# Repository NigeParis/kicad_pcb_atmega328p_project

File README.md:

# Schematic Bill of Materials

| Reference | Qty | Value | Footprint | Datasheet |
|-----------|-----|-------|-----------|-----------|
| C1, C2 | 2 | 12 pF | SMD_603 | [Yageo X7R](https://yageogroup.com/content/datasheet/asset/file/UPY-GPHC_X7R_6_3V-TO-250V) |
| C3 | 1 | 100 nF | SMD_603 | [Yageo X7R](https://yageogroup.com/content/datasheet/asset/file/UPY-GPHC_X7R_6_3V-TO-250V) |
| C4, C7 | 2 | 100 nF | SMD_603 | [Yageo X7R](https://yageogroup.com/content/datasheet/asset/file/UPY-GPHC_X7R_6_3V-TO-250V) |
| C6 | 1 | 1 µF | SMD_603 | [Yageo X7R](https://yageogroup.com/content/datasheet/asset/file/UPY-GPHC_X7R_6_3V-TO-250V) |
| D1 | 1 | LED Green | SMD_603 | [KP-1608ID](https://cdn-reichelt.de/documents/datenblatt/A500/KP-1608ID(VER.9A).pdf) |
| D2 | 1 | LED Red | SMD_603 | [KP-1608ID](https://cdn-reichelt.de/documents/datenblatt/A500/KP-1608ID(VER.9A).pdf) |
| J1 | 1 | Connector | J1_connector | [Samtec TSW](https://suddendocs.samtec.com/catalog_english/tsw_th.pdf) |
| J2 | 1 | Connector | J2_connector | [Samtec TSW](https://suddendocs.samtec.com/catalog_english/tsw_th.pdf) |
| J3 | 1 | FTDI | TSW-106-08-L-S-RA | [Samtec TSW](https://suddendocs.samtec.com/catalog_english/tsw_th.pdf) |
| R1 | 1 | 330 Ω | SMD_603 | [Yageo RC](https://yageogroup.com/content/datasheet/asset/file/PYU-RC_GROUP_51_ROHS_L) |
| R2, R3 | 2 | 10 kΩ | SMD_603 | [Yageo RC](https://yageogroup.com/content/datasheet/asset/file/PYU-RC_GROUP_51_ROHS_L) |
| SW1 | 1 | Push Switch | B3U-1000P(M) | [Omron B3U](https://omronfs.omron.com/en_US/ecb/products/pdf/en-b3u.pdf) |
| U1 | 1 | ATmega328P-A | TQFP-32 | [Microchip](https://ww1.microchip.com/downloads/aemDocuments/documents/corporate-responsibilty/environmental/material-compliance-documents/32L_TQFP_7x7x1_0mm_PT_C04-00074c.pdf) |
| Y1 | 1 | 16 MHz Crystal | SMD3225-4P | [X322516MLB4SI](https://www.lcsc.com/datasheet/C13738.pdf) |

## Summary

| Category | Count |
|----------|-------|
| Capacitors (C) | 6 |
| Diodes / LEDs (D) | 2 |
| Connectors (J) | 3 |
| Resistors (R) | 3 |
| Switch (SW) | 1 |
| Microcontroller (U) | 1 |
| Crystal (Y) | 1 |
| **Total components** | **17** |

# Pinout — Schematic (ATmega328P-A)

## J1 (12-pin, left connector)

| Pin | Signal |
|-----|--------|
| 12  | TXO    |
| 11  | RXI    |
| 10  | RST    |
| 9   | GND    |
| 8   | D2     |
| 7   | D3     |
| 6   | D4     |
| 5   | D5     |
| 4   | D6     |
| 3   | D7     |
| 2   | D8     |
| 1   | D9     |

---

## J2 (12-pin, right connector)

| Pin | Signal |
|-----|--------|
| 1   | RAW    |
| 2   | GND    |
| 3   | RST    |
| 4   | VCC    |
| 5   | A3     |
| 6   | A2     |
| 7   | A1     |
| 8   | A0     |
| 9   | SCK    |
| 10  | MISO   |
| 11  | MOSI   |
| 12  | D10    |

---

## J3 — FTDI (6-pin)

| Pin | Signal |
|-----|--------|
| 6   | GND    |
| 5   | GND    |
| 4   | VCC    |
| 3   | RXI    |
| 2   | TXO    |
| 1   | DTR    |

## 0603 SMD LED

**Imperial:** 0603 | **Metric equivalent:** 1608  
**Dimensions:** 1.6 × 0.8 × 0.8 mm (L × W × H)

### Top View

```
           1.6 mm
   ┌───────────────────┐
   │                   │  0.8 mm
   │   ╔═══════════╗   │
   │   ║    DIE    ║   │
   │   ╚═══════════╝   │
   │                   │
   └───────────────────┘
   [+]              [-]
  Anode           Cathode
```

### Dimensions Summary

| Parameter        | Value      |
|-----------------|------------|
| Length (L)       | 1.6 mm     |
| Width (W)        | 0.8 mm     |
| Height (H)       | 0.8 mm     |
| Pad size (each)  | ~0.8 × 0.9 mm |
| Pad pitch        | ~0.8 mm    |

### Notes
- Machine assembly strongly recommended; hand-soldering possible but challenging
- Typical forward current: 20 mA
- Typical forward voltage: 2.0–3.5 V (color-dependent)
- Cathode typically marked with a dot, triangle, or band on the package

## Soldered another PCB but even smaller </br>
The atmega328P-au was hard to do, had to resolder it 5 times until placed exactly on the pads.</br>
size of the MCU is 7mm x 7mm and 32 pads </br>
example size of a LED 

# SMD LED Package Dimensions: 0402 & 0603

> Imperial package codes — dimensions in **millimeters (mm)**

---

## 0402 SMD LED

**Imperial:** 0402 | **Metric equivalent:** 1005  
**Dimensions:** 1.0 × 0.5 × 0.5 mm (L × W × H)

### Top View

```
        1.0 mm
   ┌─────────────┐
   │             │  0.5 mm
   │  ╔═══════╗  │
   │  ║  DIE  ║  │
   │  ╚═══════╝  │
   │             │
   └─────────────┘
   [+]         [-]
  Anode      Cathode
```

### Dimensions Summary

| Parameter        | Value     |
|-----------------|-----------|
| Length (L)       | 1.0 mm    |
| Width (W)        | 0.5 mm    |
| Height (H)       | 0.5 mm    |
| Pad size (each)  | ~0.5 × 0.5 mm |
| Pad pitch        | ~0.6 mm   |

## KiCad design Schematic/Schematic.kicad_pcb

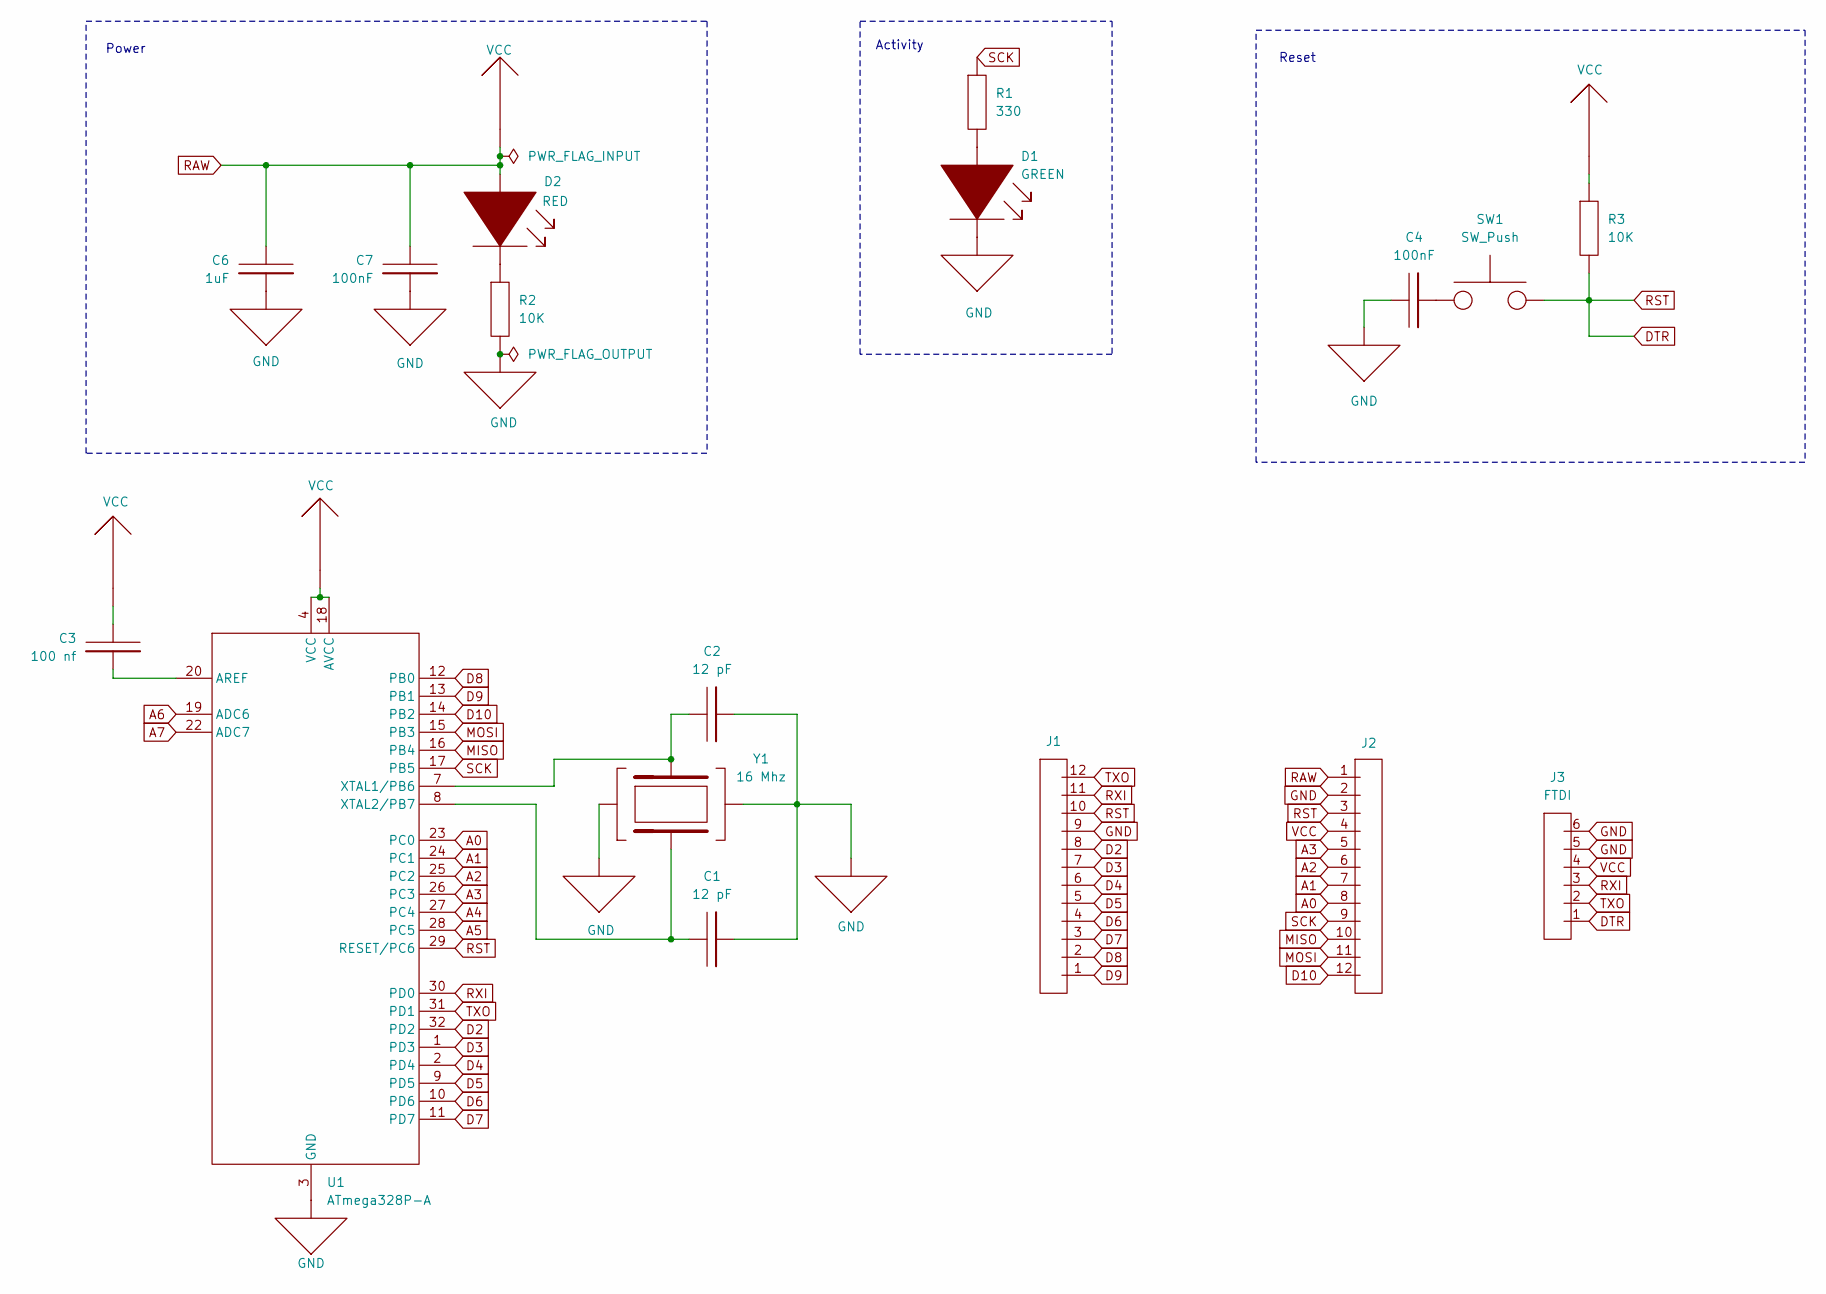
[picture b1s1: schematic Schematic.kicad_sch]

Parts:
C1, C2: 12 pF; SMD_603
C3: 100 nf; SMD_603
C4, C7: 100nF; SMD_603
C6: 1uF; SMD_603
D1: GREEN; SMD_603
D2: RED; SMD_603
J1: J1_connector
J2: J2_connector
J3: FTDI; FDTI_conector_TSW-106-08-L-S-RA
R1: 330; SMD_603
R2, R3: 10K; SMD_603
SW1: SW_Push; interupter_SMD_B3U-1000P(M)
U1: ATmega328P-A; atMega328P
Y1: 16 Mhz; Oscillator_SMD3225-4P_X322516MLB4SI

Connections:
A0: J2.8, U1.23 (PC0)
A1: J2.7, U1.24 (PC1)
A2: J2.6, U1.25 (PC2)
A3: J2.5, U1.26 (PC3)
A4: U1.27 (PC4)
A5: U1.28 (PC5)
A6: U1.19 (ADC6)
A7: U1.22 (ADC7)
D2: J1.8, U1.32 (PD2)
D3: J1.7, U1.1 (PD3)
D4: J1.6, U1.2 (PD4)
D5: J1.5, U1.9 (PD5)
D6: J1.4, U1.10 (PD6)
D7: J1.3, U1.11 (PD7)
D8: J1.2, U1.12 (PB0)
D9: J1.1, U1.13 (PB1)
D10: J2.12, U1.14 (PB2)
DTR: J1.10, J2.3, J3.1, R3.2, SW1.2, U1.29 (RESET/PC6)
GND: C1.2, C2.2, C4.1, C6.2 (GND), C7.2, D1.2, J1.9, J2.2, J3.5, J3.6, R2.2, U1.3 (GND), U1.5, U1.21, Y1.2, Y1.4
MISO: J2.10, U1.16 (PB4)
MOSI: J2.11, U1.15 (PB3)
unnamed: C4.2, SW1.1
unnamed: D1.1, R1.2
unnamed: D2.2, R2.1
unnamed: C3.2, U1.20 (AREF)
unnamed: C2.1, U1.7 (XTAL1/PB6), Y1.1
unnamed: C1.1, U1.8 (XTAL2/PB7), Y1.3
RXI: J1.11, J3.3, U1.30 (PD0)
SCK: J2.9, R1.1, U1.17 (PB5)
TXO: J1.12, J3.2, U1.31 (PD1)

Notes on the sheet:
Power
Reset
Activity

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
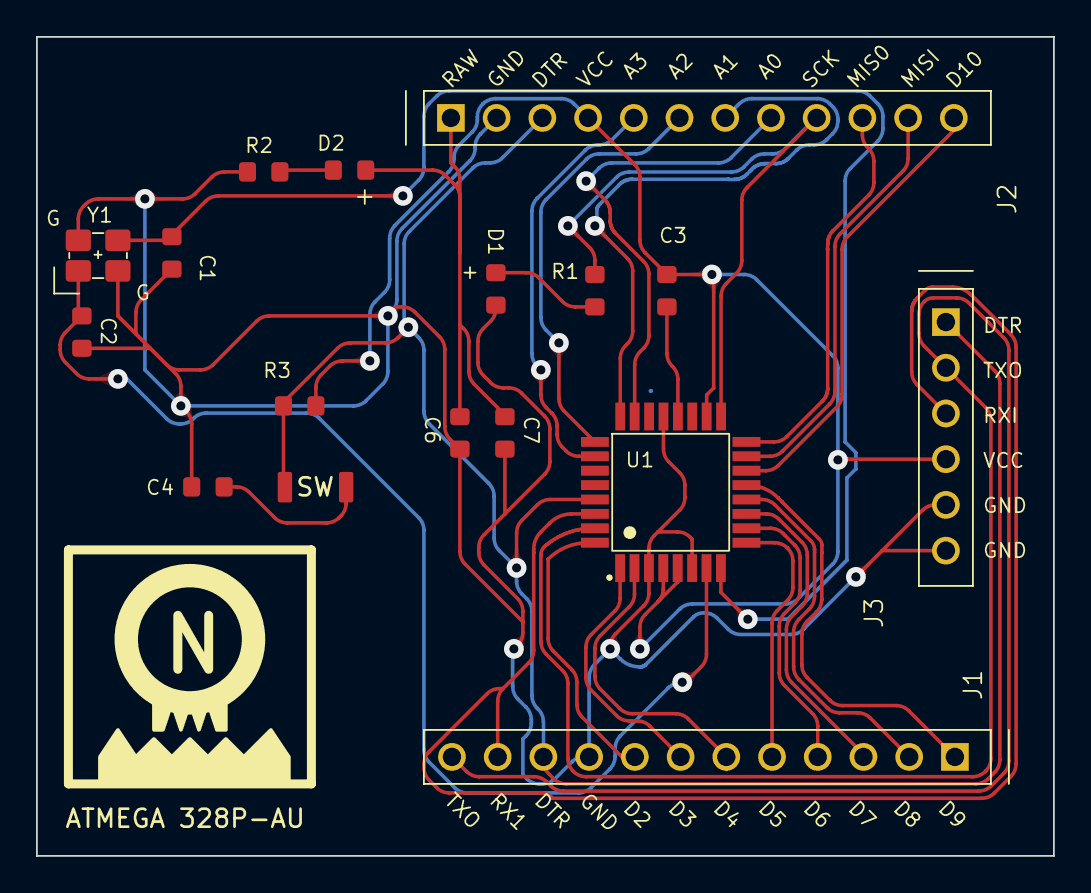
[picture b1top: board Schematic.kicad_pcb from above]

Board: 2 copper layers, 56.5 x 45.5 mm, 16 parts (0 on the bottom side), 27 nets.

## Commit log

2026-05-14 New file
2026-05-14 symbol lib
2026-05-14 error PCB done 12 warning to do
2026-05-14 warnings still to do
2026-05-15 pcb working
2026-05-15 finished
2026-05-16 updated board
2026-05-17 updated silk screen
2026-05-17 lib update
2026-05-20 readme
2026-05-23 Add images to README for enhanced visualization
    Added two images to the README for better visualization.
2026-05-23 Add additional images to README
2026-05-23 Update image link in README.md
    Replaced an image link in the README with a new one.
2026-05-23 Document soldering experience with smaller PCB
    Added a section about soldering a smaller PCB and challenges faced.
2026-05-23 Update README with component drawings and sizes
    Added top view drawings for 0603 and 0402 components, including dimensions and images.
2026-05-23 Remove top view drawings for 0603 and 0402
    Removed top view drawings for 0603 and 0402 components from the README.
2026-05-23 Add 0603 SMD LED specifications to README
    Added detailed specifications and diagrams for the 0603 SMD LED, including dimensions, notes, and top view drawings.
2026-05-23 Document 0402 SMD LED dimensions and drawings
    Added detailed dimensions and top view drawings for 0402 SMD LED package.
